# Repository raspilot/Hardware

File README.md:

#树莓派飞控RasPilot#

###RasPilot硬件参数###
特性
* 支持树莓派1 A+/B+；树莓派2 B+
* STM32F103 failsafe co-processor
* ardupilot飞控代码
* pixhawk接口兼容
* USB(RPi) / Servo Rail BEC / Power Module三路电源输入

传感器
* ST Micro L3GD20H 16位陀螺仪
* ST Micro LSM303D 14位加速度计/磁力计
* Invensense MPU 6000 3轴陀螺仪/加速度计
* MEAS MS5611 气压计

接口
* 2x UART
* 1x CAN
* 8x PWM
* Spektrum DSM / DSM2 / DSM-X® Satellite 兼容接收机
* Futaba S.BUS® 兼容输入输出
* PPM sum 接收机
* RSSI（PWM或电压）输入
* 1x I2C
* 3.3V & 6.6V A/D输入
* 安全开关
* 蜂鸣器接口
* 板载三色LED

###硬件安装和接线###
1 安装外壳。如下图，用铜柱和螺母将树莓派固定在底壳上。插上飞控扩展板，再用螺丝固定上壳。<br>

<br>
<br>
2 接口说明：<br>
<br>

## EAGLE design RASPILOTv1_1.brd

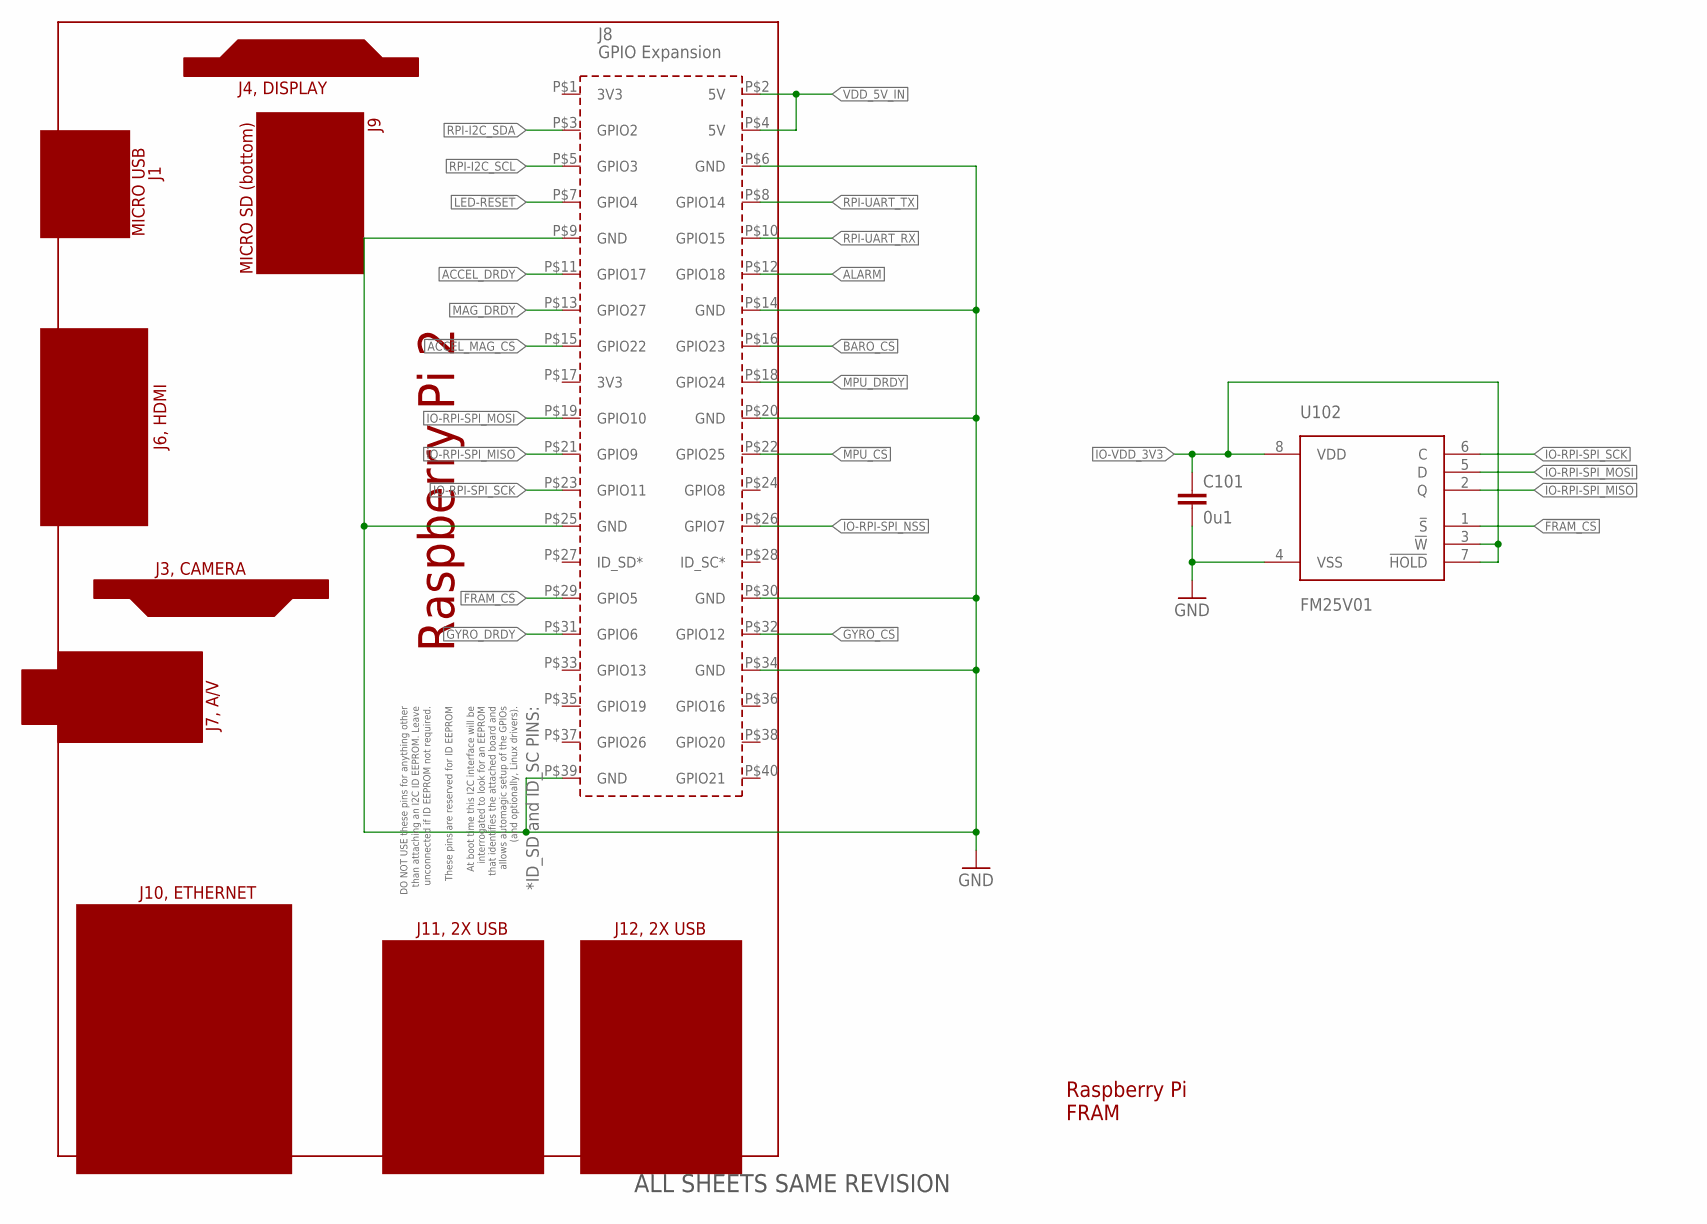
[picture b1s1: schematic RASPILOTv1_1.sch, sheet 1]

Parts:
C101: 0u1; 0402-CAP; PARTNO CC0402ZRY5V7BB104
U101: RPI2
U102: FM25V01; SO08; PARTNO FM25V01-G

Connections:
!ACCEL_MAG_CS: U101.P$15 (GPIO22); also elsewhere on the board
!BARO_CS: U101.P$16 (GPIO23); also elsewhere on the board
!FRAM_CS: U101.P$29 (GPIO5), U102.1 (!S)
!GYRO_CS: U101.P$32 (GPIO12); also elsewhere on the board
!MPU_CS: U101.P$22 (GPIO25); also elsewhere on the board
ACCEL_DRDY: U101.P$11 (GPIO17); also elsewhere on the board
ALARM: U101.P$12 (GPIO18); also elsewhere on the board
GND: C101.P$2 (2), U101.P$6 (GND), U101.P$9 (GND), U101.P$14 (GND), U101.P$20 (GND), U101.P$25 (GND), U101.P$30 (GND), U101.P$34 (GND), U101.P$39 (GND), U102.4 (VSS); also elsewhere on the board
GYRO_DRDY: U101.P$31 (GPIO6); also elsewhere on the board
IO-RPI-SPI_MISO: U101.P$21 (GPIO9), U102.2 (Q); also elsewhere on the board
IO-RPI-SPI_MOSI: U101.P$19 (GPIO10), U102.5 (D); also elsewhere on the board
IO-RPI-SPI_NSS: U101.P$26 (GPIO7); also elsewhere on the board
IO-RPI-SPI_SCK: U101.P$23 (GPIO11), U102.6 (C); also elsewhere on the board
IO-VDD_3V3: C101.P$1 (1), U102.3 (!W), U102.7 (!HOLD), U102.8 (VDD); also elsewhere on the board
LED-!RESET: U101.P$7 (GPIO4); also elsewhere on the board
MAG_DRDY: U101.P$13 (GPIO27); also elsewhere on the board
MPU_DRDY: U101.P$18 (GPIO24); also elsewhere on the board
RPI-I2C_SCL: U101.P$5 (GPIO3); also elsewhere on the board
RPI-I2C_SDA: U101.P$3 (GPIO2); also elsewhere on the board
RPI-UART_RX: U101.P$10 (GPIO15); also elsewhere on the board
RPI-UART_TX: U101.P$8 (GPIO14); also elsewhere on the board
VDD_5V_IN: U101.P$2 (5V), U101.P$4 (5V); also elsewhere on the board

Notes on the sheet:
Raspberry Pi FRAM
ALL SHEETS SAME REVISION

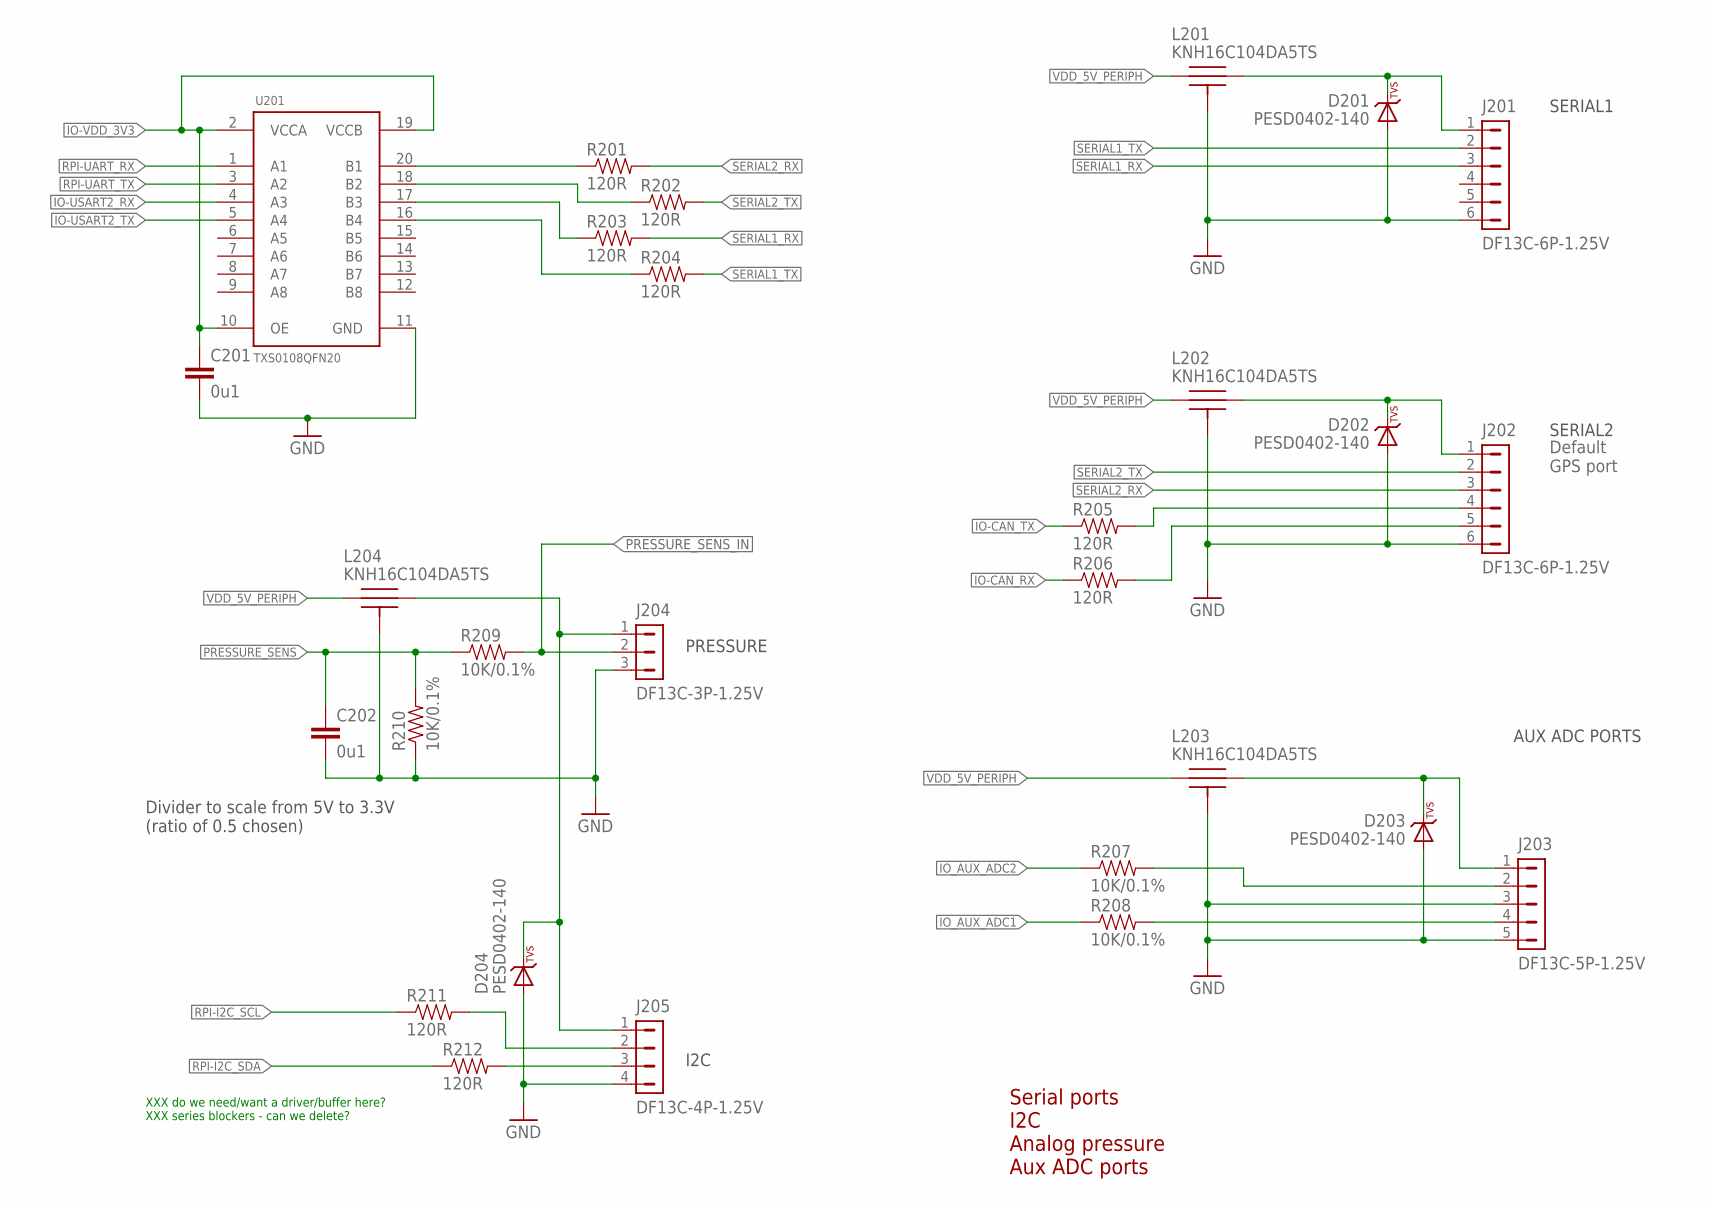
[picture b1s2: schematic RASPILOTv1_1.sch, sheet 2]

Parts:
C201, C202: 0u1; 0402-CAP; PARTNO CC0402ZRY5V7BB104
D201, D202, D203, D204: PESD0402-140; 0402-TVS; PARTNO PESD0402-140
J201, J202: DF13C-6P-1.25V; PARTNO DF13C-6P-1.25V(20)
J203: DF13C-5P-1.25V; PARTNO DF13C-5P-1.25V(20)
J204: DF13C-3P-1.25V; PARTNO DF13C-3P-1.25V(20)
J205: DF13C-4P-1.25V; PARTNO DF13C-4P-1.25V(20)
L201, L202, L203, L204: KNH16C104DA5TS; KYOCERA-KNH16-DA; PARTNO KNH16C104DA5TS
R201, R202, R203, R204, R205, R206, R211, R212: 120R; 0402-RES; PARTNO RC0402FR-07120RL
R207, R208, R209, R210: 10K/0.1%; 0402-RES; PARTNO ERA-2AEB103X
U201: TXS0108QFN20; QFN20-RGY; PARTNO TXS0108ERGYR

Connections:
FMU_AUX_ADC1_PROT1: J203.4, R208.P$2 (2)
FMU_AUX_ADC2_PROT1: J203.2, R207.P$2 (2)
GND: C201.P$2 (2), C202.P$2 (2), D201.A, D202.A, D203.A, D204.A, J201.6, J202.6, J203.3, J203.5, J204.3, J205.4, L201.P$3, L201.P$4, L201.P$5, L202.P$3, L202.P$4, L202.P$5, L203.P$3, L203.P$4, L203.P$5, L204.P$3, L204.P$4, L204.P$5, R210.P$1 (1), U201.11 (GND); also elsewhere on the board
IO-CAN_RX: R206.P$1 (1); also elsewhere on the board
IO-CAN_TX: R205.P$1 (1); also elsewhere on the board
IO-USART2_RX: U201.4 (A3); also elsewhere on the board
IO-USART2_TX: U201.5 (A4); also elsewhere on the board
IO-VDD_3V3: C201.P$1 (1), U201.2 (VCCA), U201.10 (OE), U201.19 (VCCB); also elsewhere on the board
IO_AUX_ADC1: R208.P$1 (1); also elsewhere on the board
IO_AUX_ADC2: R207.P$1 (1); also elsewhere on the board
unnamed: D203.C, J203.1, L203.P$2
unnamed: D201.C, J201.1, L201.P$2
unnamed: J205.2, R211.P$2 (2)
unnamed: J205.3, R212.P$2 (2)
unnamed: D204.C, J204.1, J205.1, L204.P$2
unnamed: J202.4, R205.P$2 (2)
unnamed: J202.5, R206.P$2 (2)
unnamed: R201.P$1 (1), U201.20 (B1)
unnamed: R202.P$1 (1), U201.18 (B2)
unnamed: R203.P$1 (1), U201.17 (B3)
unnamed: R204.P$1 (1), U201.16 (B4)
unnamed: D202.C, J202.1, L202.P$2
PRESSURE_SENS: C202.P$1 (1), R209.P$1 (1), R210.P$2 (2); also elsewhere on the board
PRESSURE_SENS_IN: J204.2, R209.P$2 (2); also elsewhere on the board
RPI-I2C_SCL: R211.P$1 (1); also elsewhere on the board
RPI-I2C_SDA: R212.P$1 (1); also elsewhere on the board
RPI-UART_RX: U201.1 (A1); also elsewhere on the board
RPI-UART_TX: U201.3 (A2); also elsewhere on the board
SERIAL1_RX: J201.3, R203.P$2 (2); also elsewhere on the board
SERIAL1_TX: J201.2, R204.P$2 (2); also elsewhere on the board
SERIAL2_RX: J202.3, R201.P$2 (2); also elsewhere on the board
SERIAL2_TX: J202.2, R202.P$2 (2); also elsewhere on the board
VDD_5V_PERIPH: L201.P$1, L202.P$1, L203.P$1, L204.P$1; also elsewhere on the board

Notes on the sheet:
Serial ports I2C Analog pressure Aux ADC ports
SERIAL1
SERIAL2
Default GPS port
AUX ADC PORTS
PRESSURE
XXX do we need/want a driver/buffer here? XXX series blockers - can we delete?
I2C
Divider to scale from 5V to 3.3V (ratio of 0.5 chosen)

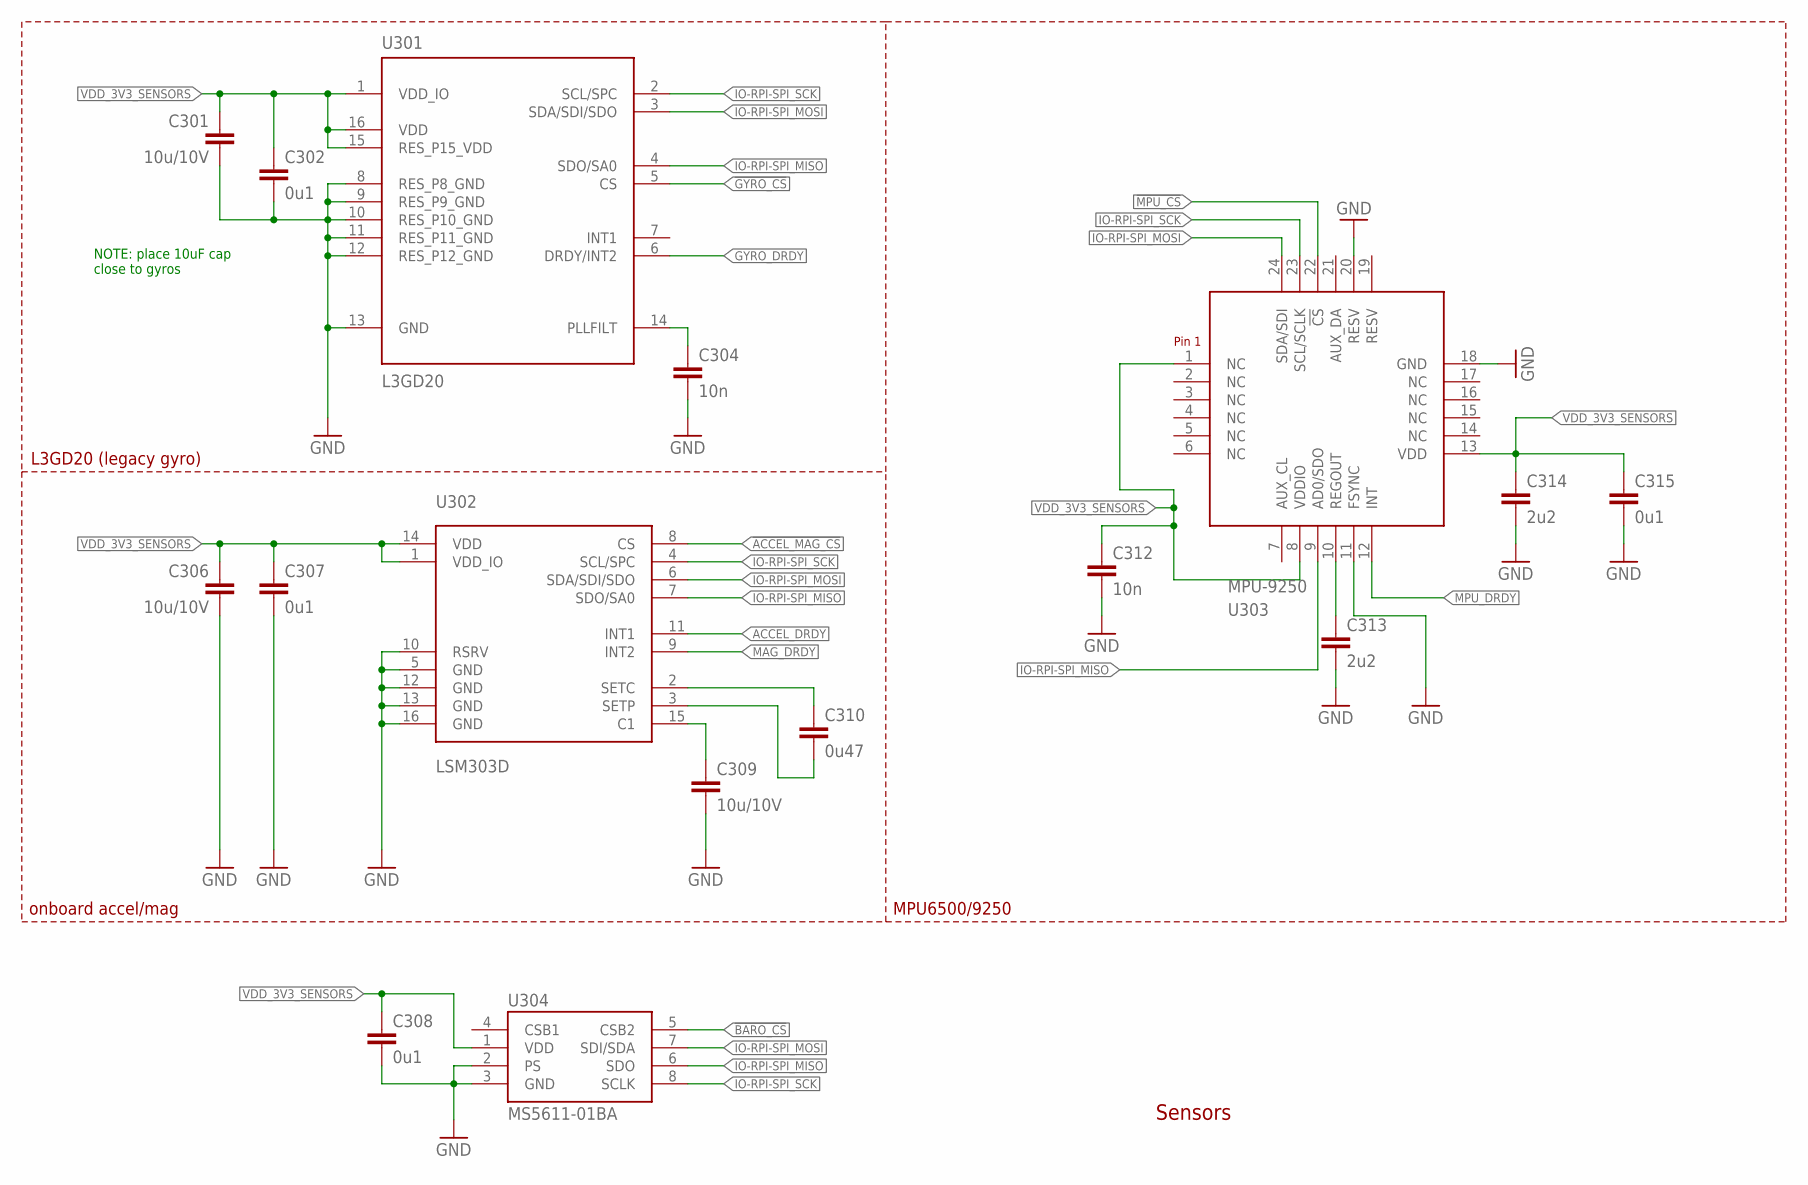
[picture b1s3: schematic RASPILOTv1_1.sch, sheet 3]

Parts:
C301, C306, C309: 10u/10V; 0805-CAP; PARTNO CC0805ZKY5V6BB106
C302, C307, C308, C315: 0u1; 0402-CAP; PARTNO CC0402ZRY5V7BB104
C304: 10n; 0402-CAP; PARTNO CC0402KRX7R7BB103
C310: 0u47; 0402-CAP; PARTNO C1005X5R1C474K050BC
C312: 10n; 0603-CAP; PARTNO C0603C103J5RAC7411
C313: 2u2; 0603-CAP; PARTNO C1608X6S1C225K080AC
C314: 2u2; 0603-CAP
U301: L3GD20; L3G4200DH-MAN; PARTNO L3GD20
U302: LSM303D; LGA-16L; PARTNO LSM303D
U303: MPU-9250; MPU-6500; PARTNO MPU-9250
U304: MS5611-01BA; PARTNO MS5611-01BA

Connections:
!ACCEL_MAG_CS: U302.8 (CS); also elsewhere on the board
!BARO_CS: U304.5 (CSB2); also elsewhere on the board
!GYRO_CS: U301.5 (CS); also elsewhere on the board
!MPU_CS: U303.22 (!CS); also elsewhere on the board
ACCEL_DRDY: U302.11 (INT1); also elsewhere on the board
GND: C301.P$2 (2), C302.P$2 (2), C304.P$2 (2), C306.P$2 (2), C307.P$2 (2), C308.P$2 (2), C309.P$2 (2), C312.P$2 (2), C313.P$2 (2), C314.P$2 (2), C315.P$2 (2), U301.8 (RES_P8_GND), U301.9 (RES_P9_GND), U301.10 (RES_P10_GND), U301.11 (RES_P11_GND), U301.12 (RES_P12_GND), U301.13 (GND), U302.5 (GND), U302.10 (RSRV), U302.12 (GND), U302.13 (GND), U302.16 (GND), U303.11 (FSYNC), U303.18 (GND), U303.20 (RESV), U304.2 (PS), U304.3 (GND); also elsewhere on the board
GYRO_DRDY: U301.6 (DRDY/INT2); also elsewhere on the board
IO-RPI-SPI_MISO: U301.4 (SDO/SA0), U302.7 (SDO/SA0), U303.9 (AD0/SDO), U304.6 (SDO); also elsewhere on the board
IO-RPI-SPI_MOSI: U301.3 (SDA/SDI/SDO), U302.6 (SDA/SDI/SDO), U303.24 (SDA/SDI), U304.7 (SDI/SDA); also elsewhere on the board
IO-RPI-SPI_SCK: U301.2 (SCL/SPC), U302.4 (SCL/SPC), U303.23 (SCL/SCLK), U304.8 (SCLK); also elsewhere on the board
MAG_DRDY: U302.9 (INT2); also elsewhere on the board
MPU_DRDY: U303.12 (INT); also elsewhere on the board
unnamed: C309.P$1 (1), U302.15 (C1)
unnamed: C310.P$1 (1), U302.2 (SETC)
unnamed: C313.P$1 (1), U303.10 (REGOUT)
unnamed: C310.P$2 (2), U302.3 (SETP)
unnamed: C304.P$1 (1), U301.14 (PLLFILT)
VDD_3V3_SENSORS: C301.P$1 (1), C302.P$1 (1), C306.P$1 (1), C307.P$1 (1), C308.P$1 (1), C312.P$1 (1), C314.P$1 (1), C315.P$1 (1), U301.1 (VDD_IO), U301.15 (RES_P15_VDD), U301.16 (VDD), U302.1 (VDD_IO), U302.14 (VDD), U303.1 (NC), U303.8 (VDDIO), U303.13 (VDD), U304.1 (VDD); also elsewhere on the board

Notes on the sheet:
Sensors
NOTE: place 10uF cap close to gyros
L3GD20 (legacy gyro)
onboard accel/mag
MPU6500/9250

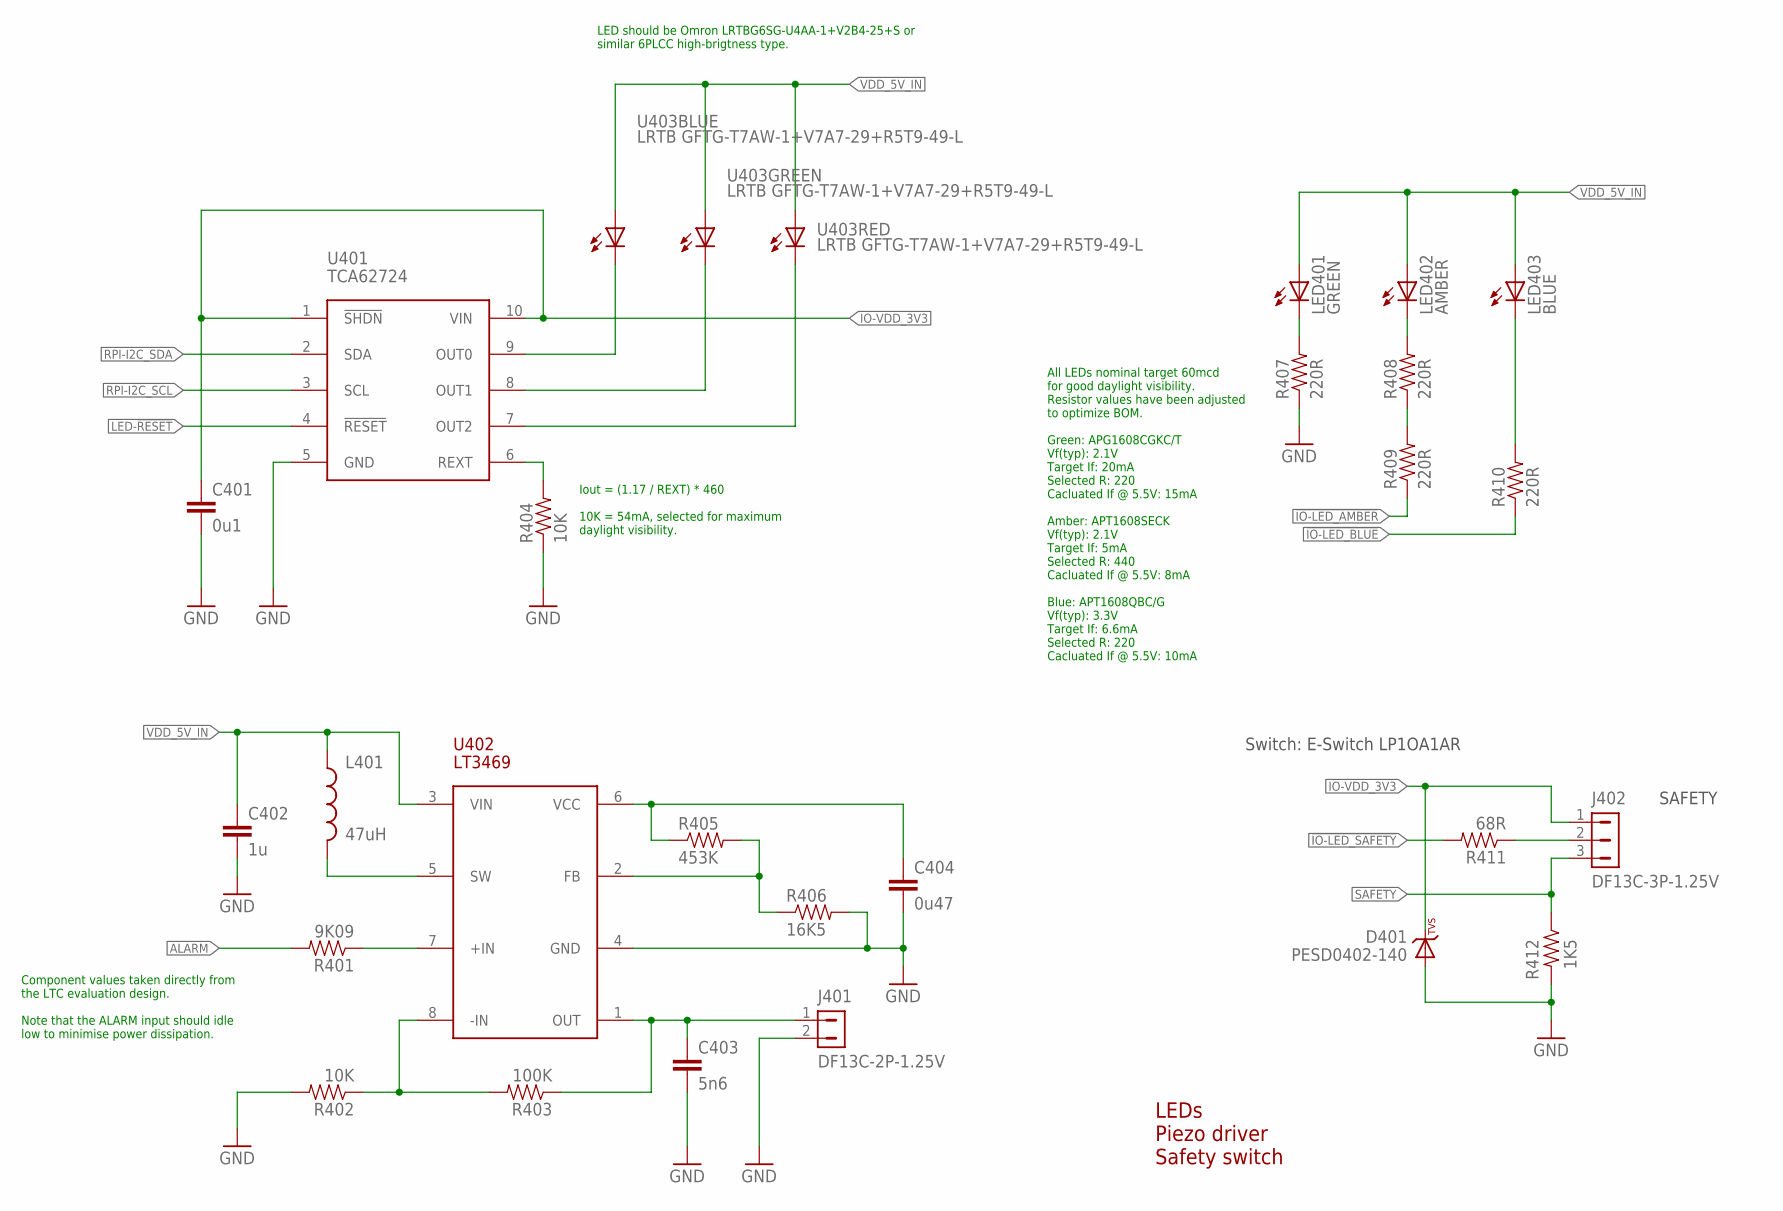
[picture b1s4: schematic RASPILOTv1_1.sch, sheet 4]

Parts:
C401: 0u1; 0402-CAP; PARTNO CC0402ZRY5V7BB104
C402: 1u; 0603-CAP; PARTNO CC0603ZRY5V7BB105
C403: 5n6; 0402-CAP; PARTNO C0402C562K5RACTU
C404: 0u47; 0402-CAP; PARTNO C1005X5R1C474K050BC
D401: PESD0402-140; 0402-TVS; PARTNO PESD0402-140
J401: DF13C-2P-1.25V; PARTNO DF13C-2P-1.25V(20)
J402: DF13C-3P-1.25V; PARTNO DF13C-3P-1.25V(20)
L401: 47uH; 0805-IND; PARTNO MLZ2012M470W
LED401: GREEN; 0603-LED; PARTNO APTD1608CGCK
LED402: AMBER; 0603-LED; PARTNO APTD1608SECK
LED403: BLUE; 0603-LED; PARTNO APTD1608QBC/D
R401: 9K09; 0402-RES; PARTNO RMCF0402FT9K09
R402, R404: 10K; 0402-RES; PARTNO RC0402FR-0710KL
R403: 100K; 0402-RES; PARTNO RC0402FR-07100KL
R405: 453K; 0402-RES; PARTNO RMCF0402FT453K
R406: 16K5; 0402-RES; PARTNO RMCF0402FT16K5
R407, R408, R409, R410: 220R; 0402-RES; PARTNO RC0402FR-07220RL
R411: 68R; 0402-RES; PARTNO ERJ-2GEJ680X
R412: 1K5; 0402-RES; PARTNO RC0402FR-071K5L
U401: TCA62724FMG; SON10; PARTNO TCA62724FMG
U402: LT3469; SOT23-8; PARTNO LT3469ETS8
U403: LRTB GFTG-T7AW-1+V7A7-29+R5T9-49-L; 6-PLCC; PARTNO LRTB GFTG-T7AW-1+V7A7-29+R5T9-49-L

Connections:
!IO-LED_AMBER: R409.P$1 (1); also elsewhere on the board
!IO-LED_BLUE: R410.P$1 (1); also elsewhere on the board
!IO-LED_SAFETY: R411.P$2 (2); also elsewhere on the board
ALARM: R401.P$2 (2); also elsewhere on the board
GND: C401.P$2 (2), C402.P$2 (2), C403.P$2 (2), C404.P$2 (2), D401.A, J401.2, R402.P$2 (2), R404.P$1 (1), R406.P$2 (2), R407.P$1 (1), R412.P$2 (2), U401.5 (GND), U402.4 (GND); also elsewhere on the board
IO-VDD_3V3: C401.P$1 (1), D401.C, J402.1, U401.1 (!SHDN), U401.10 (VIN); also elsewhere on the board
LED-!RESET: U401.4 (!RESET); also elsewhere on the board
unnamed: LED403.C, R410.P$2 (2)
unnamed: R405.P$2 (2), R406.P$1 (1), U402.2 (FB)
unnamed: R402.P$1 (1), R403.P$2 (2), U402.8 (-IN)
unnamed: C403.P$1 (1), J401.1, R403.P$1 (1), U402.1 (OUT)
unnamed: R401.P$1 (1), U402.7 (+IN)
unnamed: LED401.C, R407.P$2 (2)
unnamed: L401.P$2 (2), U402.5 (SW)
unnamed: C404.P$1 (1), R405.P$1 (1), U402.6 (VCC)
unnamed: R408.P$1 (1), R409.P$2 (2)
unnamed: LED402.C, R408.P$2 (2)
unnamed: J402.2, R411.P$1 (1)
unnamed: R404.P$2 (2), U401.6 (REXT)
RGB_LED_3: U401.9 (OUT0), U403.C1 (C)
RGB_LED_4: U401.8 (OUT1), U403.C2 (C)
RGB_LED_14: U401.7 (OUT2), U403.C3 (C)
RPI-I2C_SCL: U401.3 (SCL); also elsewhere on the board
RPI-I2C_SDA: U401.2 (SDA); also elsewhere on the board
SAFETY: J402.3, R412.P$1 (1); also elsewhere on the board
VDD_5V_IN: C402.P$1 (1), L401.P$1 (1), LED401.A, LED402.A, LED403.A, U402.3 (VIN), U403.A1 (A), U403.A2 (A), U403.A3 (A); also elsewhere on the board

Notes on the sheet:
LEDs Piezo driver Safety switch
Switch: E-Switch LP1OA1AR
SAFETY
LED should be Omron LRTBG6SG-U4AA-1+V2B4-25+S or similar 6PLCC high-brigtness type.
Iout = (1.17 / REXT) * 460 10K = 54mA, selected for maximum daylight visibility.
All LEDs nominal target 60mcd for good daylight visibility. Resistor values have been adjusted to optimize BOM. Green: APG1608CGKC/T Vf(typ): 2.1V Target If: 20mA Selected R: 220 Cacluated If @ 5.5V: 15mA Amber: APT1608SECK Vf(typ): 2.1V Target If: 5mA Selected R: 440 Cacluated If @ 5.5V: 8mA Blue: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
Component values taken directly from the LTC evaluation design. Note that the ALARM input should idle low to minimise power dissipation.

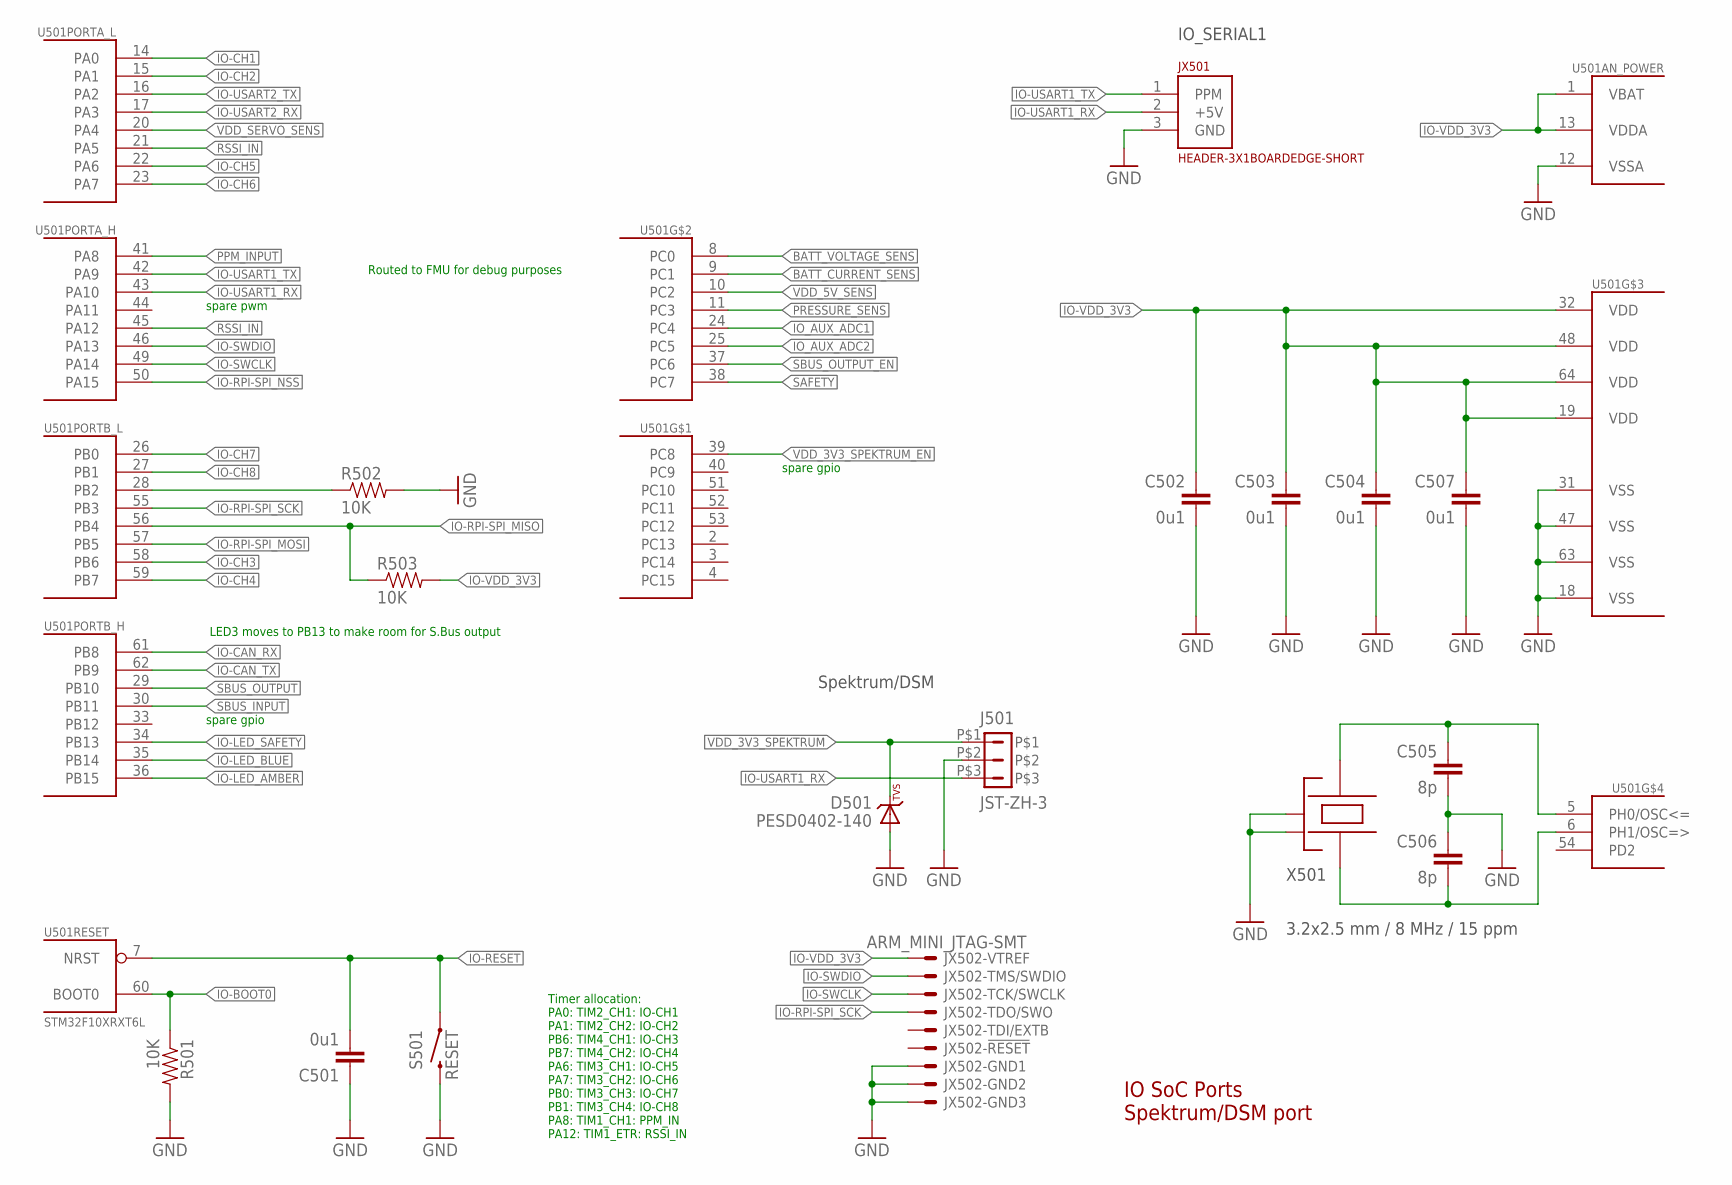
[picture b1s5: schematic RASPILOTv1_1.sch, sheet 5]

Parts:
C501, C502, C503, C504, C507: 0u1; 0402-CAP; PARTNO CC0402ZRY5V7BB104
C505, C506: 8p; 0402-CAP; PARTNO C1005C0G1H080C
D501: PESD0402-140; 0402-TVS; PARTNO PESD0402-140
J501: JST-ZH-3; JST-ZH-SMT-VERTICAL; PARTNO B3B-ZR-SM4-TF (LF)(SN)(P)
JX501: HEADER-3X1BOARDEDGE-SHORT; HEADER_3X01_SMD_H_BOARD_EDGE_SHORT
JX502: ARM_MINI_JTAG-SMT; FTSH-105-01-XXX-DV-K; PARTNO M50-3900542
R501, R502, R503: 10K; 0402-RES; PARTNO RC0402FR-0710KL
S501: RESET; EVQP7J01K; PARTNO EVQ-P7J01P
U501: STM32F10XRXT6L; TQFP64
X501: 3.2x2.5 mm / 8 MHz / 15 ppm; OSCILLATOR-3.2X2.5; PARTNO NX3225SA-24.000000MHZ

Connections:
!IO-LED_AMBER: U501.36 (PB15); also elsewhere on the board
!IO-LED_BLUE: U501.35 (PB14); also elsewhere on the board
!IO-LED_SAFETY: U501.34 (PB13); also elsewhere on the board
!SBUS_OUTPUT_EN: U501.37 (PC6); also elsewhere on the board
BATT_CURRENT_SENS: U501.9 (PC1); also elsewhere on the board
BATT_VOLTAGE_SENS: U501.8 (PC0); also elsewhere on the board
GND: C501.P$1 (1), C502.P$2 (2), C503.P$2 (2), C504.P$2 (2), C505.P$2 (2), C506.P$1 (1), C507.P$2 (2), D501.A, J501.P$2, JX501.3 (GND), JX502.3, JX502.5, JX502.9, R501.P$2 (2), R502.P$2 (2), S501.B3 (2), U501.12 (VSSA), U501.18 (VSS), U501.31 (VSS), U501.47 (VSS), U501.63 (VSS), X501.2 (NC_2), X501.4 (NC_4); also elsewhere on the board
IO-!RESET: C501.P$2 (2), S501.A1 (1), U501.7 (NRST); also elsewhere on the board
IO-BOOT0: R501.P$1 (1), U501.60 (BOOT0); also elsewhere on the board
IO-BOOT1: R502.P$1 (1), U501.28 (PB2)
IO-CAN_RX: U501.61 (PB8); also elsewhere on the board
IO-CAN_TX: U501.62 (PB9); also elsewhere on the board
IO-CH1: U501.14 (PA0); also elsewhere on the board
IO-CH2: U501.15 (PA1); also elsewhere on the board
IO-CH3: U501.58 (PB6); also elsewhere on the board
IO-CH4: U501.59 (PB7); also elsewhere on the board
IO-CH5: U501.22 (PA6); also elsewhere on the board
IO-CH6: U501.23 (PA7); also elsewhere on the board
IO-CH7: U501.26 (PB0); also elsewhere on the board
IO-CH8: U501.27 (PB1); also elsewhere on the board
IO-RPI-SPI_MISO: R503.P$1 (1), U501.56 (PB4); also elsewhere on the board
IO-RPI-SPI_MOSI: U501.57 (PB5); also elsewhere on the board
IO-RPI-SPI_NSS: U501.50 (PA15); also elsewhere on the board
IO-RPI-SPI_SCK: JX502.6, U501.55 (PB3); also elsewhere on the board
IO-SWCLK: JX502.4, U501.49 (PA14)
IO-SWDIO: JX502.2, U501.46 (PA13)
IO-USART1_RX: J501.P$3, JX501.2 (+5V), U501.43 (PA10)
IO-USART1_TX: JX501.1 (PPM), U501.42 (PA9)
IO-USART2_RX: U501.17 (PA3); also elsewhere on the board
IO-USART2_TX: U501.16 (PA2); also elsewhere on the board
IO-VDD_3V3: C502.P$1 (1), C503.P$1 (1), C504.P$1 (1), C507.P$1 (1), JX502.1, R503.P$2 (2), U501.1 (VBAT), U501.13 (VDDA), U501.19 (VDD), U501.32 (VDD), U501.48 (VDD), U501.64 (VDD); also elsewhere on the board
IO_AUX_ADC1: U501.24 (PC4); also elsewhere on the board
IO_AUX_ADC2: U501.25 (PC5); also elsewhere on the board
unnamed: C506.P$2 (2), U501.6 (PH1/OSC=>), X501.1
unnamed: C505.P$1 (1), U501.5 (PH0/OSC<=), X501.3
PPM_INPUT: U501.41 (PA8); also elsewhere on the board
PRESSURE_SENS: U501.11 (PC3); also elsewhere on the board
RSSI_IN: U501.21 (PA5), U501.45 (PA12); also elsewhere on the board
SAFETY: U501.38 (PC7); also elsewhere on the board
SBUS_INPUT: U501.30 (PB11); also elsewhere on the board
SBUS_OUTPUT: U501.29 (PB10); also elsewhere on the board
VDD_3V3_SPEKTRUM: D501.C, J501.P$1; also elsewhere on the board
VDD_3V3_SPEKTRUM_EN: U501.39 (PC8); also elsewhere on the board
VDD_5V_SENS: U501.10 (PC2); also elsewhere on the board
VDD_SERVO_SENS: U501.20 (PA4); also elsewhere on the board

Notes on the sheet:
IO SoC Ports Spektrum/DSM port
LED3 moves to PB13 to make room for S.Bus output
Routed to FMU for debug purposes
IO_SERIAL1
Spektrum/DSM
Timer allocation: PA0: TIM2_CH1: IO-CH1 PA1: TIM2_CH2: IO-CH2 PB6: TIM4_CH1: IO-CH3 PB7: TIM4_CH2: IO-CH4 PA6: TIM3_CH1: IO-CH5 PA7: TIM3_CH2: IO-CH6 PB0: TIM3_CH3: IO-CH7 PB1: TIM3_CH4: IO-CH8 PA8: TIM1_CH1: PPM_IN PA12: TIM1_ETR: RSSI_IN
spare pwm
spare gpio

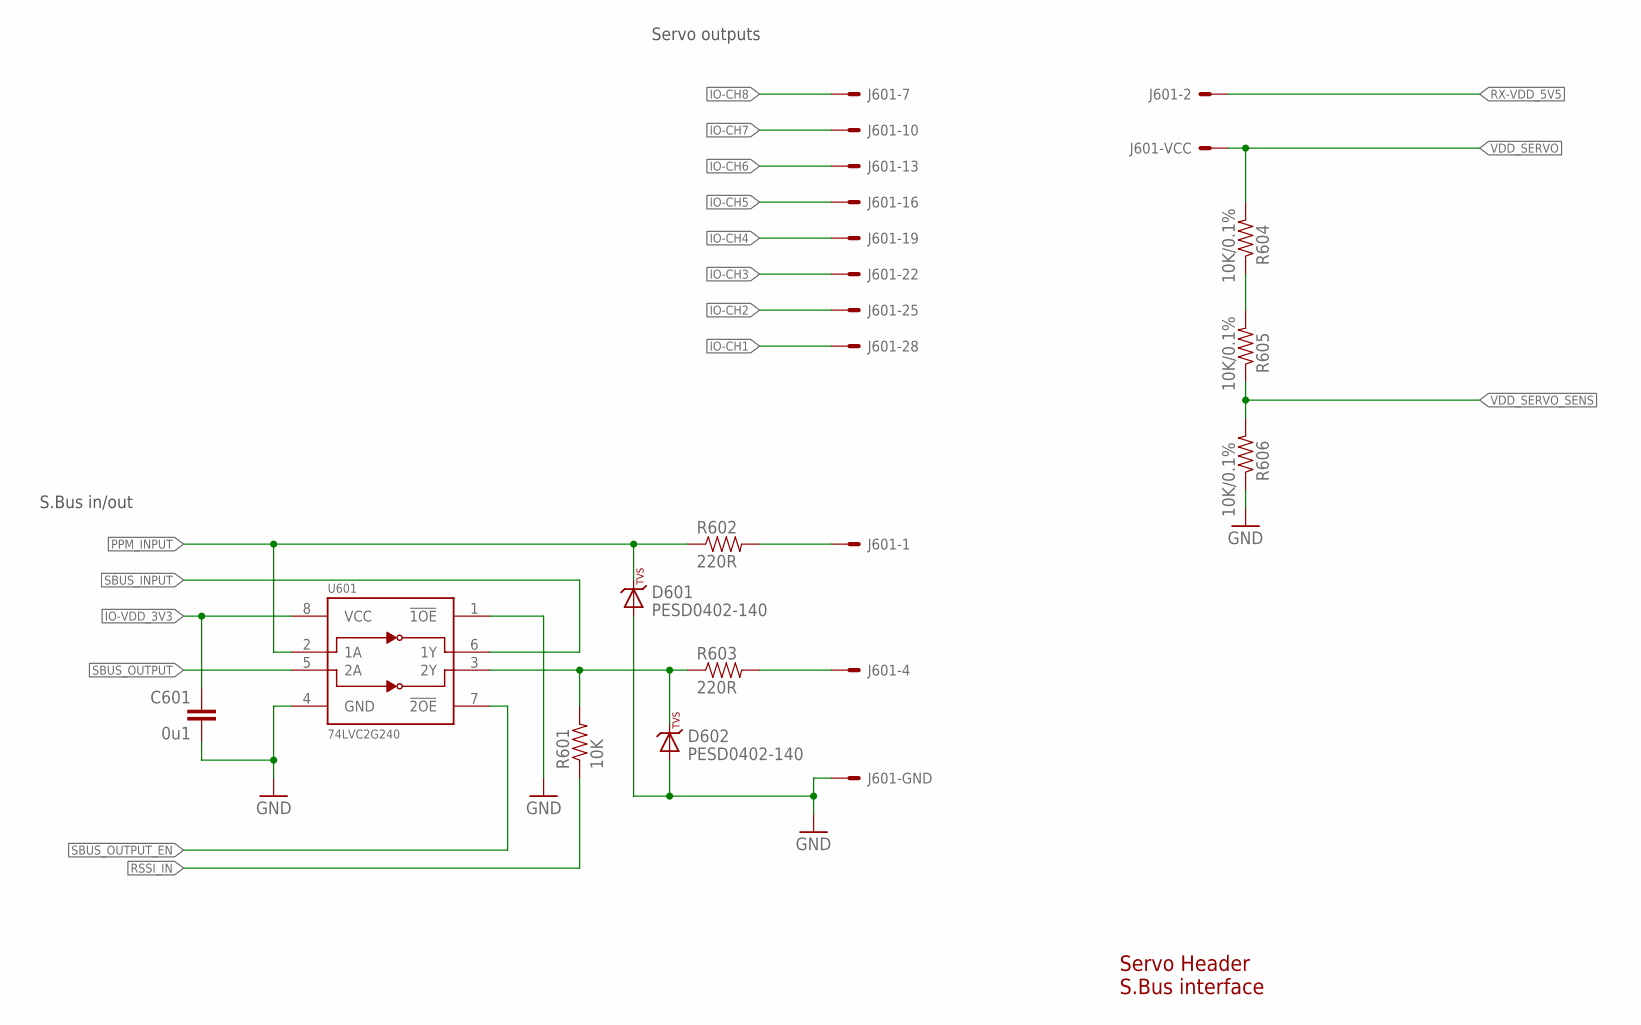
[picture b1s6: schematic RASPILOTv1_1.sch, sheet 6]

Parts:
C601: 0u1; 0402-CAP; PARTNO CC0402ZRY5V7BB104
D601, D602: PESD0402-140; 0402-TVS; PARTNO PESD0402-140
J601: HEADER-3X10; 3X10RA
R601: 10K; 0402-RES; PARTNO RC0402FR-0710KL
R602, R603: 220R; 0402-RES; PARTNO RC0402FR-07220RL
R604, R605, R606: 10K/0.1%; 0402-RES; PARTNO ERA-2AEB103X
U601: 74LVC2G240; TSSOP8_SOT505-2; PARTNO 74LVC2G240DP,125

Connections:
!SBUS_OUTPUT_EN: U601.7 (!2OE); also elsewhere on the board
GND: C601.P$2 (2), D601.A, D602.A, J601.3, J601.6, J601.9, J601.12, J601.15, J601.18, J601.21, J601.24, J601.27, J601.30, R606.P$1 (1), U601.1 (!1OE), U601.4 (GND); also elsewhere on the board
IO-CH1: J601.28; also elsewhere on the board
IO-CH2: J601.25; also elsewhere on the board
IO-CH3: J601.22; also elsewhere on the board
IO-CH4: J601.19; also elsewhere on the board
IO-CH5: J601.16; also elsewhere on the board
IO-CH6: J601.13; also elsewhere on the board
IO-CH7: J601.10; also elsewhere on the board
IO-CH8: J601.7; also elsewhere on the board
IO-VDD_3V3: C601.P$1 (1), U601.8 (VCC); also elsewhere on the board
unnamed: R604.P$1 (1), R605.P$2 (2)
unnamed: D602.C, R601.P$2 (2), R603.P$1 (1), U601.3 (2Y)
unnamed: J601.4, R603.P$2 (2)
PPM-SBUS-PROT: J601.1, R602.P$2 (2)
PPM_INPUT: D601.C, R602.P$1 (1), U601.2 (1A); also elsewhere on the board
RSSI_IN: R601.P$1 (1); also elsewhere on the board
RX-VDD_5V5: J601.2; also elsewhere on the board
SBUS_INPUT: U601.6 (1Y); also elsewhere on the board
SBUS_OUTPUT: U601.5 (2A); also elsewhere on the board
VDD_SERVO: J601.5, J601.8, J601.11, J601.14, J601.17, J601.20, J601.23, J601.26, J601.29, R604.P$2 (2); also elsewhere on the board
VDD_SERVO_SENS: R605.P$1 (1), R606.P$2 (2); also elsewhere on the board

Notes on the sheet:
Servo Header S.Bus interface
S.Bus in/out
Servo outputs

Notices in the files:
parts and their libraries:
SparkFun-Retired: Licensing:Creative Commons ShareAlike 4.0 International - https://creativecommons.org/licenses/by-sa/4.0
